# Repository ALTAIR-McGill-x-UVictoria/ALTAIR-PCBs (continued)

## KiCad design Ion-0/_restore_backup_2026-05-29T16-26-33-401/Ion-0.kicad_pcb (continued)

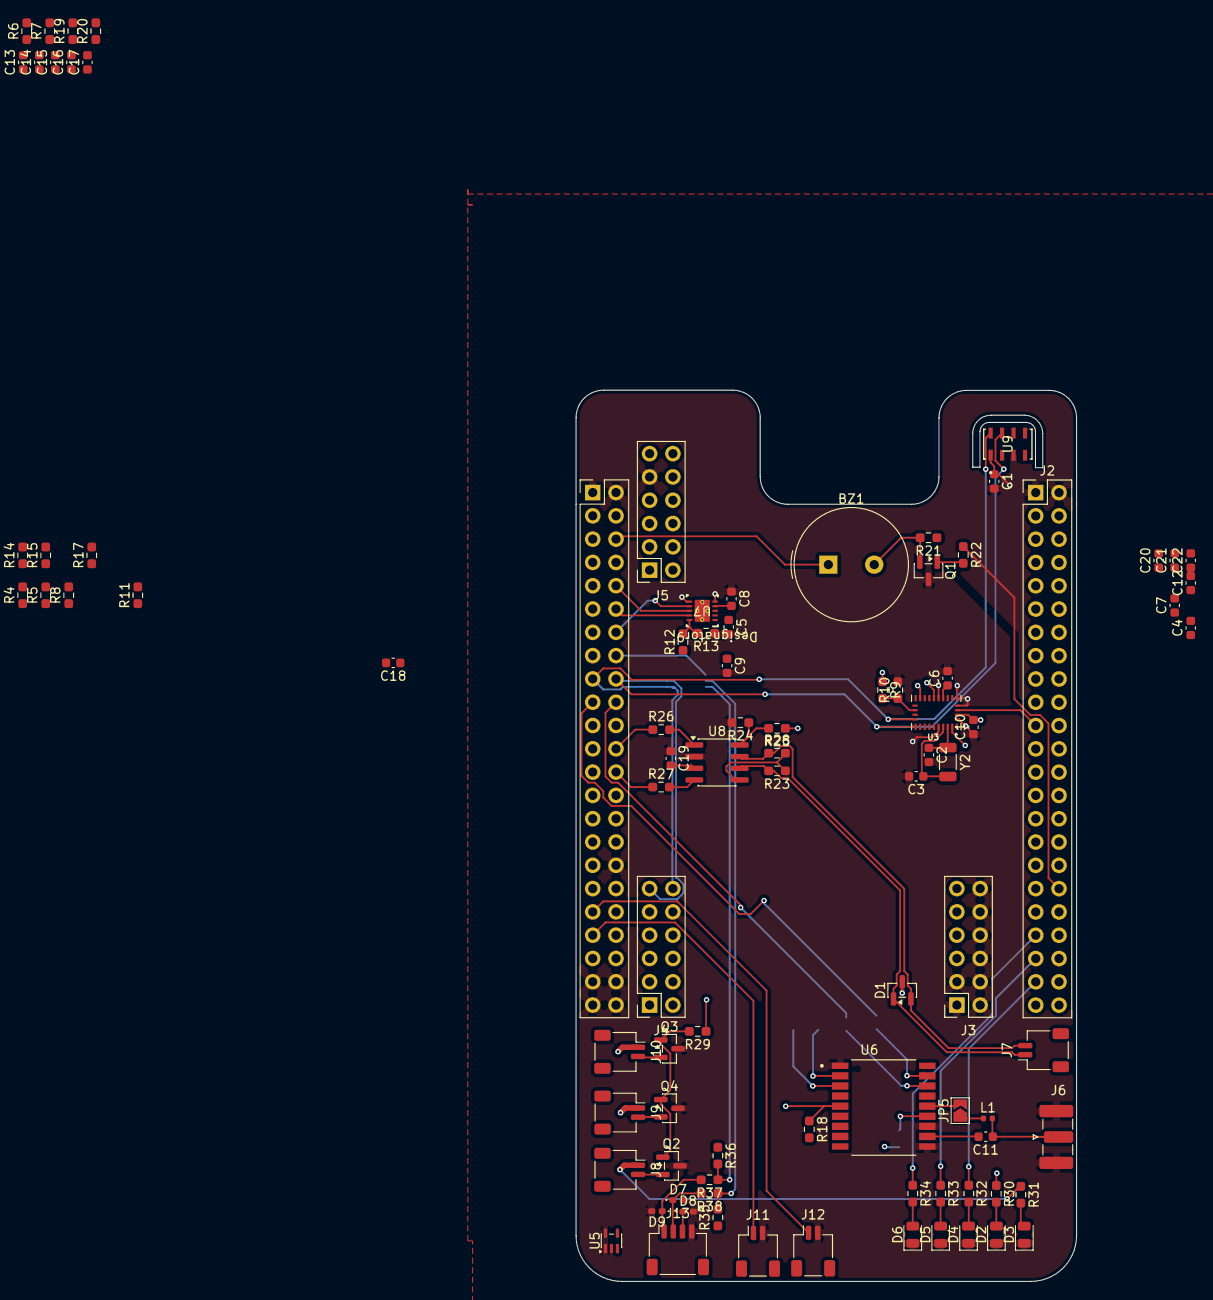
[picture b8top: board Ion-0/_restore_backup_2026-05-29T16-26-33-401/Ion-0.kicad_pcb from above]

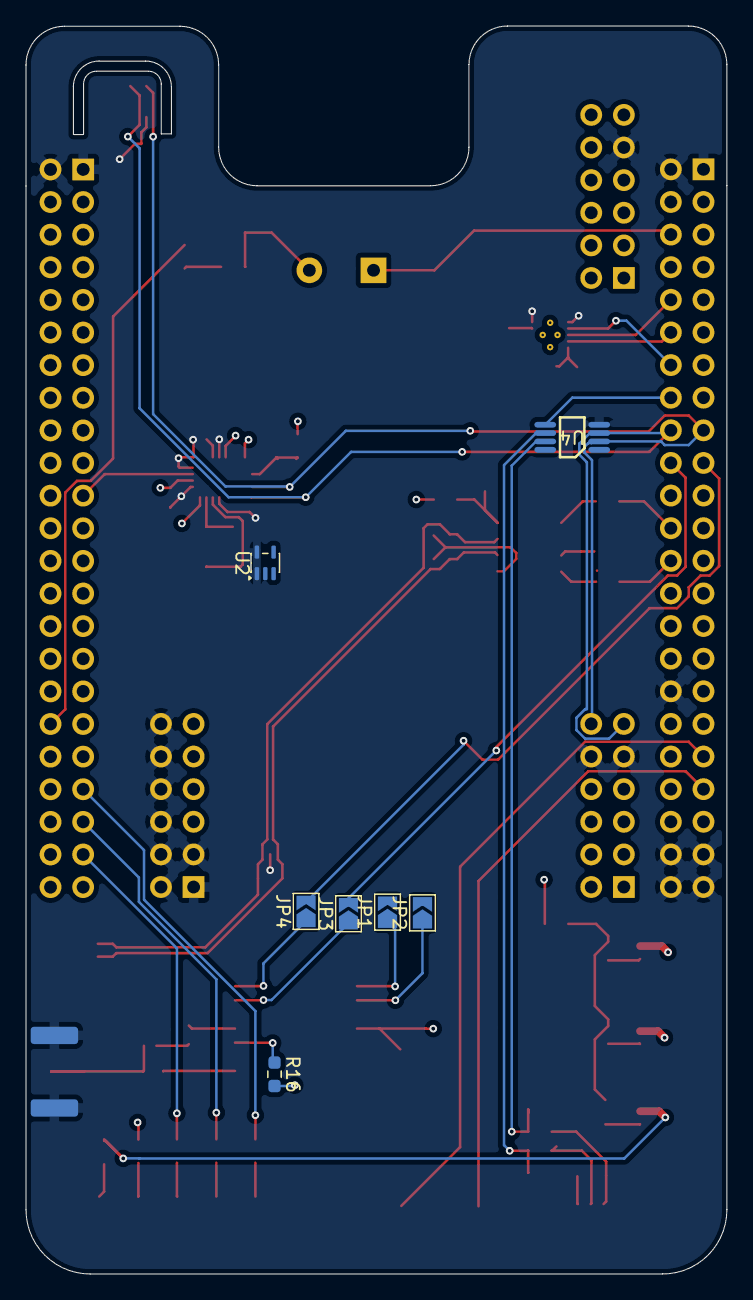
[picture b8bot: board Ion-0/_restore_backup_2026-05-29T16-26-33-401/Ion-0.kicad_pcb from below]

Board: 4 copper layers, 54.6 x 97.2 mm, 99 parts (7 on the bottom side), 78 nets.

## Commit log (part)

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2026-03-18 working on it
2026-03-23 split into two PCBs
2026-03-25 made b2b footprint
2026-03-26 termination
2026-03-28 LMAO
2026-03-30 damo was here
2026-03-30 working on interface board
2026-03-31 almomst done
2026-03-31 updated 3d models for power
2026-03-31 working on BOM
2026-04-01 complete BOM
2026-04-01 exported files, working on BOM orders
2026-04-01 ordered
2026-04-02 update bom
2026-05-12 bringup updates
2026-05-23 new sensor board hat for the beaglebone green called MIF-CHAB, pronounced my hab
2026-05-26 revision 0.1 - added debug stuff, CAN interface, I2C buffer
2026-05-26 Fixed symbol library
2026-05-27 library fix, no 3d models tho
2026-05-28 init commit for layout
2026-05-28 fixed pins to correct position
2026-05-29 midway through
2026-05-29 finished tracing, need to fix m3 holes, text, impedance match antenna, via stiching
2026-06-05 terminator
2026-06-06 restarting layout
2026-06-06 the board is done but still needs to be cleaned of schematic up and via stitching
2026-06-07 nothing working commit
2026-06-07 WAR IS OVER
2026-06-07 reduced gps trace length
2026-06-07 terminatotr
2026-06-07 fixes in silkscreen
2026-06-08 allignment fix for power board
2026-06-08 up to date
2026-06-08 CAN trace fix
2026-06-09 fixing power board
2026-06-09 power rev 1.1
2026-06-10 starting interface layout
2026-06-11 added stepper driver
2026-06-12 interface layout done
2026-06-12 fixed interface schematic
2026-06-12 connectors fixes
2026-06-12 fixes in the schematic, made it better
2026-06-12 version 0.8 - stepper driver included and better detailled schematic
2026-06-12 BUZZER NEVER DIES
2026-06-12 Revert "update"
    This reverts commit ded726db31db978a67aba241c9369c22f126eee0.
2026-06-13 fixes
2026-06-13 arduino PCB
2026-06-13 some fixes idk
2026-06-15 silkscreen changes
2026-06-16 generated production files for Ion-0
2026-06-16 slight correction in GPS line
2026-06-16 added production files
2026-06-16 jlc order
2026-06-16 fixed impedance mismatch
2026-06-17 new production files
2026-06-17 still trying to order. last minute fixes
2026-06-17 updating boms
2026-06-19 BOM ORDER
